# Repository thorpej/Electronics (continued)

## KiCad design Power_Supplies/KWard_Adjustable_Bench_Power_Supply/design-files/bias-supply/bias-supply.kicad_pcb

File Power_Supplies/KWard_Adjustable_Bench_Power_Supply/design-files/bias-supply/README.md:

# Bias supply

The bias supply board provides an adjustable (0 - -100V), current-limted
(approximately 30mA) negative bias supply for the device-under-test, typically
used to bias the power output stages of an amplifier.

The board is powered by a a Triad F4-120 power transfomer, which is nominally
rated as 115Vac -> 120Vac @ 50ma.

The AC input is rectified by a Rectron DB107 diode bridge chip, filtered, and
fed to a MJE5371 PNP power transistor which provides a low-impedance voltage
reference by pinning its base to -150V using a Zener diode.  This -150V reference
voltage is then fed to a second MJE5371, whose base voltage is controlled by a
fixed 39K resistor and a precision 10-turn potentiometer (see note below),
providing the variable bias voltage output.  A 1µF film cap at the output shunts
out any noise.

Current limiting is provided by a small KSA1013 PNP transistor (connected to the
base of the second MJE5371) and a 22 Ohm resistor.  As the current increases, the
voltage drop across the 22 Ohm resistor increases, which gradually turns on the
KSA1013, which pulls the base of the second MJE5371 closer to GND (more positive),
thus making the bias voltage output less negative.  Note that this is a gradual
effect; if there is significant load on the bias supply, it will become gradually
more difficult to pull the voltage further negative.

Beacuse the second MJE5371 can drop considerable voltage depending on the desired
bias output voltage selected, it can dissipate quite a bit more heat than the first
MJE5371 used as the voltage reference.  It is therefore mounted to a much beefier
heat sink than the first MJE5371.  Space for a small fin-type heat sink for the
first MJE5371 is provided, along with a specific Aavid part known to fit the
footprint.  Other small fin-type heat sinks may also fit in the alloted space.
However, it is important that the two heat sinks DO NOT TOUCH, unless the MJE5371s
are mounted using a TO-220 insulated mounting kit (plastic screw bushing + mica sheet).

The board includes protection diodes for the 3 transistors as well as the output.

Note: The voltage adjustment divider also contains a 10 Ohm fixed resistor to "back-stop"
the negative bias voltage because without it, the voltage can become positive with
the potentiometer at the full CCW position in simulation.  With this resistor in-place,
you may not be able to get the bias voltage to exactly 0V.  This may vary slightly
due to manufacturing tolerances.  If this is problematic for your application, feel
free to experiment with different resistor values, or to bypass the resistor entirely
with a jumper wire.

The board has standard M3 mounting holes, and is intended to be mounted on the
back of the PSU front panel using stand-offs.

## Parts list

Note that all resistors are 2W metal film unless specified otherwise.  The Mouser
part numbers provided here for standard resistors are for Vishay PR02-series, which
fit the footprints on the board.

* 1x Triad F4-120 power transformer or equivalent.
_Mouser part number 553-F4-120._
* 2x 2-position screw terminal blocks, 5.08mm pitch (CUI TB007-508-02BE or equivalent).
_Mouser part number 490-TB007-508-02BE._
* 2x 3-position screw terminal blocks, 5.08mm pitch (CUI TB006-508-03BE or equivalent).
_Mouser part number 490-TB006-508-03BE._
* 1x Rectron DB107 diode bridge (can substitude a Rectron DB105 or DB106, if desired).
_Mouser part number 583-DB107._
* 2x 220µF 250V electrolytic capacitor, up to 18mm diameter, 7.50mm lead spacing.
_Mouser part number 647-UCS2E221MHD._
* 1x 1µF 250V polypropylene film capacitor, rectangular form-factor, 18mm x 11mm, lead
spacing 15mm.
_Mouser part number 871-B32672L2105J000._
* 1x 1N5385B 150V 5W Zener diode.
_Mouser part number 863-1N5383BG._
* 4x 1N4007 diode.
_Mouser part number 621-1N4007G-T._
* 2x MJE5731 PNP transistors (TO-220 package).
_Mouser part number 863-MJE5731G._
* 1x KSA1013 PNP transistor (TO-92L package).
_Mouser part number 512-KSA1013YBU._
* 1x 100 Ohm resistor.
_Mouser part number 594-5083NW100R0JA100._
* 1x 330K Ohm resistor.
_Mouser part number 594-5083NW330K0J._
* 1x 10K Ohm resistor.
_Mouser part number 594-5083NW10K00J._
* 1x 39K Ohm resistor.
_Mouser part number 594-5083NW39K00J._
* 1x 10 Ohm resistor.
_Mouser part number 594-5083NW10R00J._
* 1x 22 Ohm resistor.
_Mouser part number 594-5083NW22R00J._
* 1x 1M Ohm resistor.
_Mouser part number 594-5083NW1M000F._
* 1x 100K 2W 10-turn panel-mount precision potentiometer.
_Mouser part number 652-3590S-2-104L._
* 1x Aavid Thermalloy ML33G TO-220 heat sink.
_Mouser part number 532-ML33G._
* 1x Aavid 577202B04000G TO-220 heat sink, or suitable substitute that
fits the available board space.
_Mouser part number 532-577202B04000G._
* **Optional but recommended** 2x insulated TO-220 mounting kit, such as
the Aavid 4880SG.
_Mouser part number 532-4880SG._

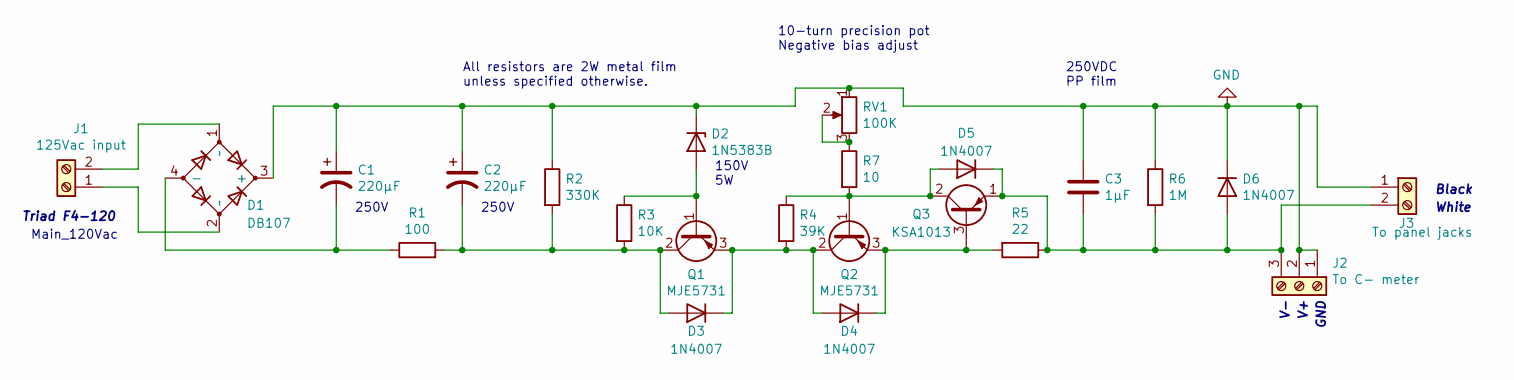
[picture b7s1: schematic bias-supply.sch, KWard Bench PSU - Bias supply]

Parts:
C1, C2: 220µF; CP_Radial_D18.0mm_P7.50mm; Mouser 647-UCS2E221MHD
C3: 1µF; C_Rect_L18.0mm_W11.0mm_P15.00mm_FKS3_FKP3; Mouser 871-B32672L2105J000
D1: DB107; Diode_Bridge_DIP-4_W7.62mm_P5.08mm
D2: 1N5383B; D_DO-201_P15.24mm_Horizontal; Mouser 863-1N5383BG
D3, D4, D5: 1N4007; D_DO-41_SOD81_P10.16mm_Horizontal
D6: 1N4007; D_DO-41_SOD81_P10.16mm_Horizontal; Mouser 621-1N4007G-T
J1: 125Vac input; TerminalBlock_bornier-2_P5.08mm
J2: To C- meter; TerminalBlock_bornier-3_P5.08mm
J3: To panel jacks; TerminalBlock_bornier-2_P5.08mm
Q1, Q2: MJE5731; TO-220-3_Vertical; Mouser 863-MJE5731G
Q3: KSA1013; TO-92L; Mouser 512-KSA1013YBU
R1: 100; R_Axial_DIN0411_L9.9mm_D3.6mm_P15.24mm_Horizontal; Mouser 594-5083NW100R0JA100
R2: 330K; R_Axial_DIN0411_L9.9mm_D3.6mm_P15.24mm_Horizontal; Mouser 594-5083NW330K0J
R3: 10K; R_Axial_DIN0411_L9.9mm_D3.6mm_P15.24mm_Horizontal; Mouser 594-5083NW10K00J
R4: 39K; R_Axial_DIN0411_L9.9mm_D3.6mm_P15.24mm_Horizontal; Mouser 594-5083NW39K00J
R5: 22; R_Axial_DIN0411_L9.9mm_D3.6mm_P15.24mm_Horizontal; Mouser 594-5083NW22R00J
R6: 1M; R_Axial_DIN0411_L9.9mm_D3.6mm_P15.24mm_Horizontal; Mouser 594-5083NW1M000F
R7: 10; R_Axial_DIN0309_L9.0mm_D3.2mm_P2.54mm_Vertical; Mouser 594-5083NW10R00J
RV1: 100K; TerminalBlock_bornier-3_P5.08mm

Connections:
GND: C1.1, C2.1, C3.1, D1.3 (+), D2.1 (K), D6.1 (K), J2.1, J2.2, J3.1, R2.1, R6.1, RV1.1
unnamed: C1.2, D1.4 (-), R1.1
unnamed: C2.2, D3.2 (A), Q1.2 (C), R1.2, R2.2, R3.2
unnamed: C3.2, D5.1 (K), D6.2 (A), J2.3, J3.2, Q3.1 (E), R5.1, R6.2
unnamed: D1.1 (~~), J1.2
unnamed: D1.2 (~~), J1.1
unnamed: D2.2 (A), Q1.1 (B), R3.1
unnamed: D3.1 (K), D4.2 (A), Q1.3 (E), Q2.2 (C), R4.2
unnamed: D4.1 (K), Q2.3 (E), Q3.3 (B), R5.2
unnamed: D5.2 (A), Q2.1 (B), Q3.2 (C), R4.1, R7.2
unnamed: R7.1, RV1.2, RV1.3

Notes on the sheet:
250V
150V 5W
10-turn precision pot Negative bias adjust
250VDC PP film
White
Black
All resistors are 2W metal film unless specified otherwise.
Triad F4-120
Main_120Vac
GND

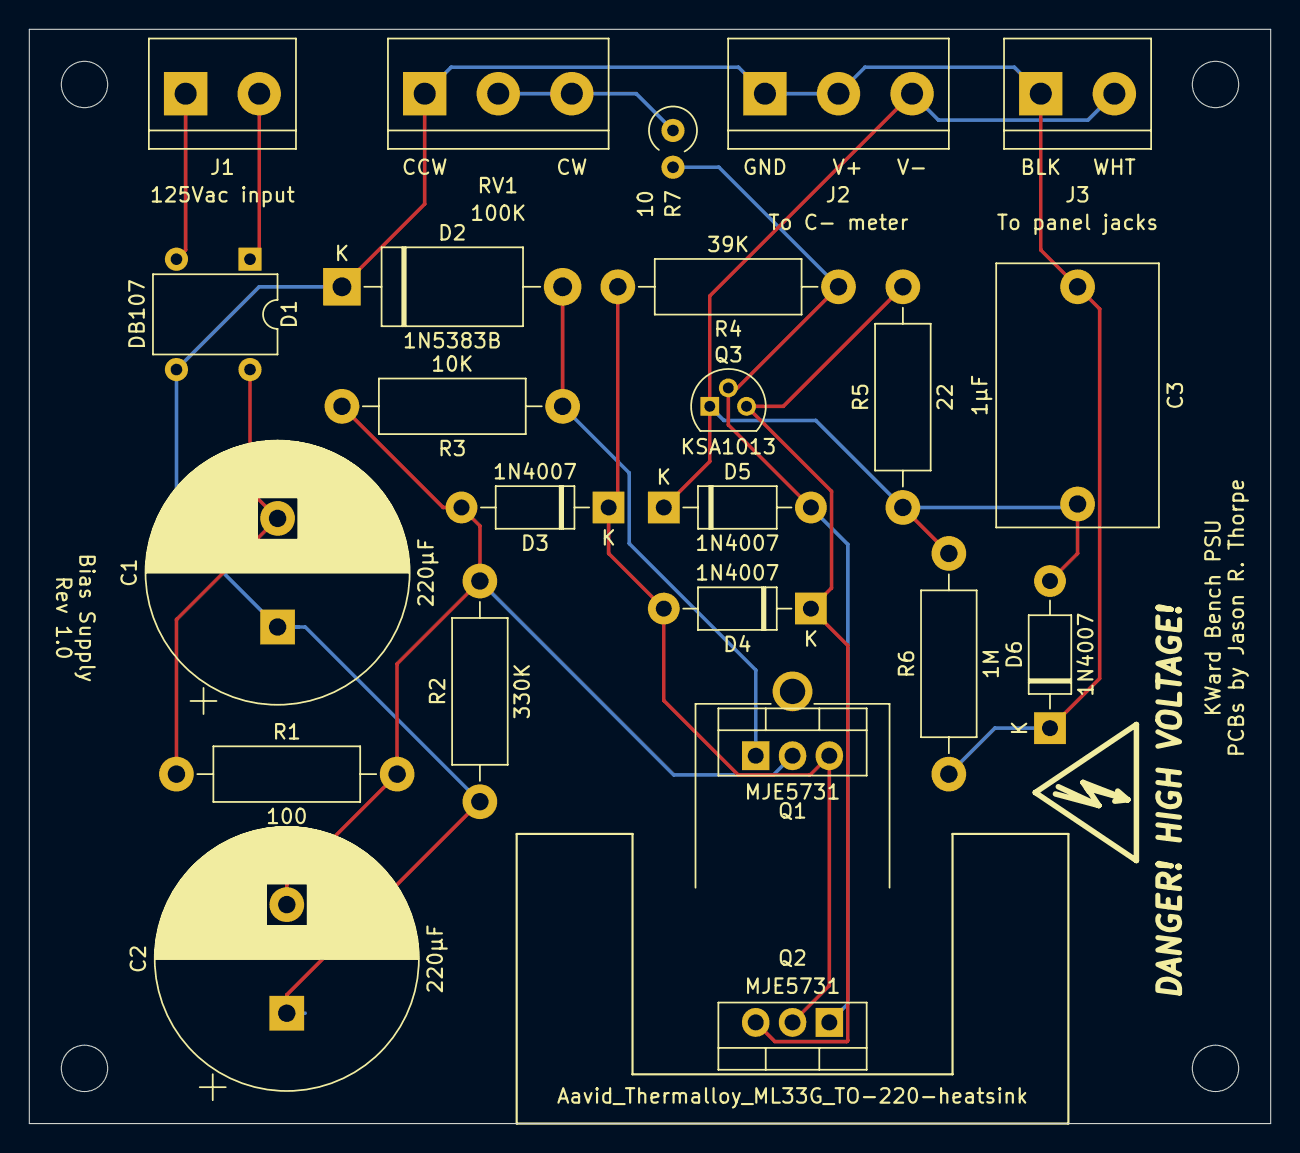
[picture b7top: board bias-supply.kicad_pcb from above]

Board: 2 copper layers, 85.7 x 75.6 mm, 24 parts (0 on the bottom side), 11 nets.

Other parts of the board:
**REF: Aavid_Thermalloy_ML33G_TO-220-heatsink

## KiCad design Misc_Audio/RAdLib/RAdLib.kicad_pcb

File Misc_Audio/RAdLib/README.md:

# The RAdLib - An OPL2 FM synthesizer board for Raspberry Pi

**NOTE: This is a work-in-progress.  Watch this space for updates.**

This project is an attempt to bring the glorious sound of the classic
AdLib sound card to the Raspberry Pi (and other single-board computers
with a compatible 40-pin GPIO header).  If you think this is a dumb
idea, you're right!  The purpose of the project is really to teach myself
and practice some design techniques and apply them to a piece of obsolete
technology with no practical application other than one of simple amusement.

My intent is for the board to be, to the extent possible, "100% software-
compatible" with the original AdLib, which was esentially the thinnest of
wrappers around the YM3812 "OPL2" synthesizer chip.  Practically speaking,
this means exposing all of the same capabilities of the OPL2 synthesizer
to the host system; obviously there are going to be some software-visible
differences because the Raspberry Pi does not have an ISA bus.

The OPL2 synthesizer circuit is essentially lifted from Sergey Malinov's
[ISA OPL2 Card](http://www.malinov.com/Home/sergeys-projects/isa-opl2-card),
and the analog section of the board is inspired by it, but has been reworked
to fit within the constraints of the Raspberry Pi's power supply.  The
bus interface, of course, is completely different.

## Bus Interface

The original AdLib is an 8-bit ISA card with fairly straight-forward address
decode logic that allows it to be accessed at one of 4 jumper-selectable
I/O-mapped addresses.  It occupies 2 bytes of I/O space.  The address decode
logic on the board is responsible for asserting the OPL2's /CS signal, and
the OPL2's /RD, /WR, and A0 signals are responsible for selecting which
internal register the bus cycle will access.  The OPL2 also has 8 data
signals, D[0-7].  /CS, /RD, and /WR are active-low.  The OPL2 responds
to these signals as follows:

* /CS=0, /RD=1, /WR=0, A0=0: write to the OPL2 index register (selects
which internal register to access)
* /CS=0, /RD=1, /WR=0, A0=1: write to the OPL2 data register (writes
this data to the previously selected internal register)
* /CS=0, /RD=0, /WR=1, A0=0: read the OPL2 status register
* /CS=1, /RD=x, /WR=x, A0=x: D[0-7] are high-Z
* The result of all other signal combinations is undefined.

As you can see, sending a command to the OPL2 requires two write cycles
(one for the index register, one for the data register).

The original AdLib is also capable of interrupting the host in the event
the host wants to use the built-in timers.  This was achieved by routing
the open-drain /IRQ signal of the OPL2 though a 7404 inverter to drive
one of the jumper-selected active-high ISA IRQ lines.

On the original AdLib, the clock is derived from the ISA bus clock.  We
have no such clock on the Raspberry Pi, so the clock is provided by a
3.58MHz crystal oscillator module in a DIP-8 "half-can" package.

Even though practically all software for the OPL2 treats it as a write-only
device, there is a status register that is accessed when you issue a read
cycle with the A0 pin low.  The only documented function of this status
register is to report if the OPL2 is asserting its interrupt line,
and which of the 2 timers is responsible for the interrupt.  I wasn't able
to find any (modern) software that actually uses the timer (and interrupt)
capabilities of the OPL2.  The only use for reading the status register I've
seen is for using undocumented bits to determine if the chip is an OPL2 or
OPL3.  But one of my goals was for the board to be able to do everything the
original AdLib could do, and that included reading the status register and
generating an interrupt.

At the bare minimum, there are 8 data lines and 5 non-data lines (A0,
READ/WRITE, CS, RESET, and IRQ) needed to interface to the OPL2.
Technically, the OPL2 has separate inputs for READ and WRITE, but a single
signal from the host can be used to generate both.  The data lines need to
be bi-directional.  A0, READ/WRITE, CS, and RESET are host->OPL2, and IRQ
is OPL2->host.  All of the control signals except A0 are active-low on the
OPL2.

I initially considered using SPI as the data interface between the host
and the RAdLib.  But this would have required an additional logic to trigger
loading of parallel-to-serial shift register from the OPL D[0..7] pins at
the right time after the OPL /CS and /RD signals are asserted in the read
case (which as stated before, is exceedingly rare).  The software overhead
of setting up the SPI transfers for each OPL2 register access also seemed
like it could be excessive and possibly difficult to avoid unpredictable
(software) timing artifacts.  It would have been hardware-intensive, as well;
2 shift registers (one for each direction) would have been required.

So, I scrapped the SPI idea and decided to go with a naive
drive-each-Dx-pin-directly approach.

Before we get into the details, here are the signals between the Raspberry
Pi and the OPL2 used by the RAdLib:

* D[0-7]: Bi-directional data signals
* A0: Address bit 0 (active high)
* READ: Indicates that the bus cycle is a READ access (active high)
* /CS: Chip-select (active low)
* /RST: OPL2 reset (active low)

The main challenge interfacing the OPL2 to the Raspberry Pi is that the
OPL2 is a CMOS device that uses 5V TTL logic levels, whereas the Raspberry
Pi's GPIO uses 3.3V CMOS logic levels.  This is not a problem for writing
to the OPL2, because a 3.3V CMOS logical "1" is 2.4V, which is above the
2V input threshold of TTL.  However, it is a problem if you want to be
able to read the OPL2 status register.  To support reading the OPL2 data
lines (which may output voltages in excess of 3.3V) safely, we need some
logic to level-shift the 5V TTL data signals from the OPL2 down to 3.3V CMOS
logic levels.  For this we use a 74LVC245A bus transceiver.  The 74LVC245A's
Vcc is connected to the 3.3V rail and has 5.5V-tolerant inputs.  The
transciever passes through the 3.3V signals on writes to the OPL2 and
level-shifts the signals from the OPL2 on reads.  The OPL2 is connected
to the "A" side of the 74LVC245A, and the Raspberry Pi is connected to
the "B" side.

The A0, /CS, and /RST control signals can be connected directly to the OPL2.

The READ signal needs to be converted into two discrete active-low control
signals for the OPL2: /RD and /WR.  Conveniently, READ being low translates
directly to /WR, and so it is directly connected to the OPL2.  We also
connect this signal to the DIR pin of the 74LVC245A.  When READ is low, B
is the input and A is the output.  When the READ signal goes high, A is
the input and B is the output.  That just leaves generating the /RD signal
at the OPL2.  This is achieved by connecting the OPL2 /RD pin to Vcc with
a 4.7K resistor and to GND using a discrete MOSFET.  The MOSFET is turned
on by the READ signal going high, which pulls the OPL2 /RD pin to GND.

## Active Filter

The original AdLib features an active low-pass filter comprised of 2
op-amps in a Butterworth configuration.  Simulation of this circuit
shows a voltage gain of 8dB with a flat response to 10KHz, is 3dB down
at 15KHz, and is 10dB down at 20KHz.

Unfortunately, the performance of this circuit relies on the headroom
afforded by the +12V/-12V split rail supply available on the ISA bus.
No such headroom is available on the Raspberry Pi; all we have is a
+5V rail.

The YM3014B DAC outputs a signal from 1/4 Vcc to 3/4 Vcc.  This means a
maximum output sine wave is centered at +2.5V and has a voltage swing of
2.5Vpp (slightly higher than a standard consumer line-level output).  This
leaves us with very little headroom to amplify the signal for the filter.

This required a re-work of the 2-stage active low-pass filter.  The reworked
filter achieves unity gain and performance similar to that of the original
filter circuit, but requires the use of a rail-to-rail op-amp; the OP495
is the most expensive part on the board.

## Audio Output Section

The original AdLib also includes an LM386 audio power amplifier IC connected
to the +12V/-12V rails to drive headphones or a small loudspeaker.  Again, the
Raspberry Pi does not have adequate power supply headroom in order to provide
any voltage gain, so we will have to be content with the 2.5Vpp swing we get
from the DAC, and rely on an external power amplifier with a line-level
input to drive a loudspeaker.  However, I still wanted to include a volume
control.  The high side of the volume control pot is AC-coupled to the output
of the filter circuit, and the wiper is AC-coupled to an emitter-follower
to isolate the volume control from the load connected to the output jack.
AC coupling is used on either side of the volume control to deep DC off of
the pot (no one likes scratchy volume controls).  The 2N3904 is biased with
a voltage divider taken off the +5V rail.  This should be capable of driving
any line-level output, and may also be able to drive headphones to some degree.

As built, unfortunately, this uses 3 large electrolytic caps to maintain
the flat frequency response, but I don't think it's the end of the world.

## Bill of Materials

You can source most of the components at Mouser.  Here are links to
individual components that fit the footprints on the board.

All resistors are 1/8W 1%.

* 6x .1uF ceramic capacitor (C1, C2, C3, C4, C201, C203) [Mouser 81-RHSN12A104K1DGH1A](https://www.mouser.com/ProductDetail/81-RHSN12A104K1DGH1A)
* 4x 10uF tantalum capacitor (C5, C6, C7, C51, C202) [Mouser 581-TAP106K016SCS](https://www.mouser.com/ProductDetail/581-TAP106K016SCS)
* 1x 680pF ceramic capacitor (C52) [Mouser 81-RCER72A681K0DBH3A](https://www.mouser.com/ProductDetail/81-RCER72A681K0DBH3A)
* 2x 1000pF ceramic capacitor (C53, C56) [Mouser 81-RCER72A102K0DBH3A](https://www.mouser.com/ProductDetail/81-RCER72A102K0DBH3A)
* 2x 100pF ceramic capacitor (C54, C57) [Mouser 594-K101K15C0GH5TK2](https://www.mouser.com/ProductDetail/594-K101K15C0GH5TK2)
* 1x 470pF ceramic capacitor (C55) [Mouser 81-RCER72A471K0DBH3A](https://www.mouser.com/ProductDetail/81-RCER72A471K0DBH3A)
* 3x 220uF electrolytic capacitor (C58, C59, C61) [Mouser 75-516D227M016MM6AE3](https://www.mouser.com/ProductDetail/75-516D227M016MM6AE3)
* 1x .047uF ceramic capacitor (C60) [Mouser 81-RCER72A473K1DBH3A](https://www.mouser.com/ProductDetail/81-RCER72A473K1DBH3A)
* 1x 10-position break-away 2.54mm vertical header (J2, J3, J4, JP1) [Mouser 538-22-28-5101](https://www.mouser.com/ProductDetail/538-22-28-5101)
* 1x Audio jack (J5) [Mouser 806-STX-31203B577C](https://www.mouser.com/ProductDetail/806-STX-31203B577C)
* 1x 2N3904 NPN transistor (Q1) [Mouser 610-2N3904](https://www.mouser.com/ProductDetail/610-2N3904)
* 1x 2N7000 N-channel MOSFET (Q201) [Mouser 512-2N700](https://www.mouser.com/ProductDetail/512-2N7000)
* 5x 10K resistor (R1, R2, R3, R4, R9) [Mouser 270-10K-RC](https://www.mouser.com/ProductDetail/270-10K-RC)
* 2x 1K resistor (R5, R7) [Mouser 270-1K-RC](https://www.mouser.com/ProductDetail/270-1K-RC)
* 1x 2.7K resistor (R6) [Mouser 270-2.7K-RC](https://www.mouser.com/ProductDetail/270-2.7K-RC)
* 3x 10R resistor (R8, R10, R11) [Mouser 270-10-RC](https://www.mouser.com/ProductDetail/270-10-RC)
* 5x 3.3K resistor (R201, R202, R203, R204, R205) [Mouser 270-3.3K-RC](https://www.mouser.com/ProductDetail/270-3.3K-RC)
* 1x 10K audio taper potentiometer (RV1) [Mouser 652-91A1A-B24-D15L](https://www.mouser.com/ProductDetail/652-91A1A-B24-D15L)
* 1x OP495 op-amp (U3) [Mouser 584-OP495GPZ](https://www.mouser.com/ProductDetail/584-OP495GPZ)
* 1x 74LVC245A bus transciever (U201) [Mouser 595-SN74LVC245ANE4](https://www.mouser.com/ProductDetail/595-SN74LVC245ANE4)
* 1x XXX 24Cxx serial EEPROM (U204) (optional)
* 1x DIP-8 3.579545MHz crystal oscillator (X1) [Mouser 520-TCH357X](https://www.mouser.com/ProductDetail/520-TCH357-X)

I sourced the female connector that mates to the Raspberry Pi from
Adafruit.  If someone has a Mouser part # for an equivalent part,
please share it with me!

* 1x Tall 2x20 female header (J1) [Adafruit 1992](https://www.adafruit.com/product/1992)

Things you'll need to find yourself (on eBay, perhaps):

* 1x Yamaha YM3812 (U1)
* 1x Yamaha YM3014B (U2)

I provisioned space for sockets for the expensive / old-stock / optional ICs.
You can get these from Jameco, Amazon, etc.

* YM3812 (U1) - DIP-24 15.24mm
* YM3014B (U2) - DIP-8 7.62mm
* OP495 (U3) - DIP-14 7.62mm
* 24Cxx (U204) (optional) - DIP-8 7.62mm

**NOTE: This is a work-in-progress.  Watch this space for updates.**

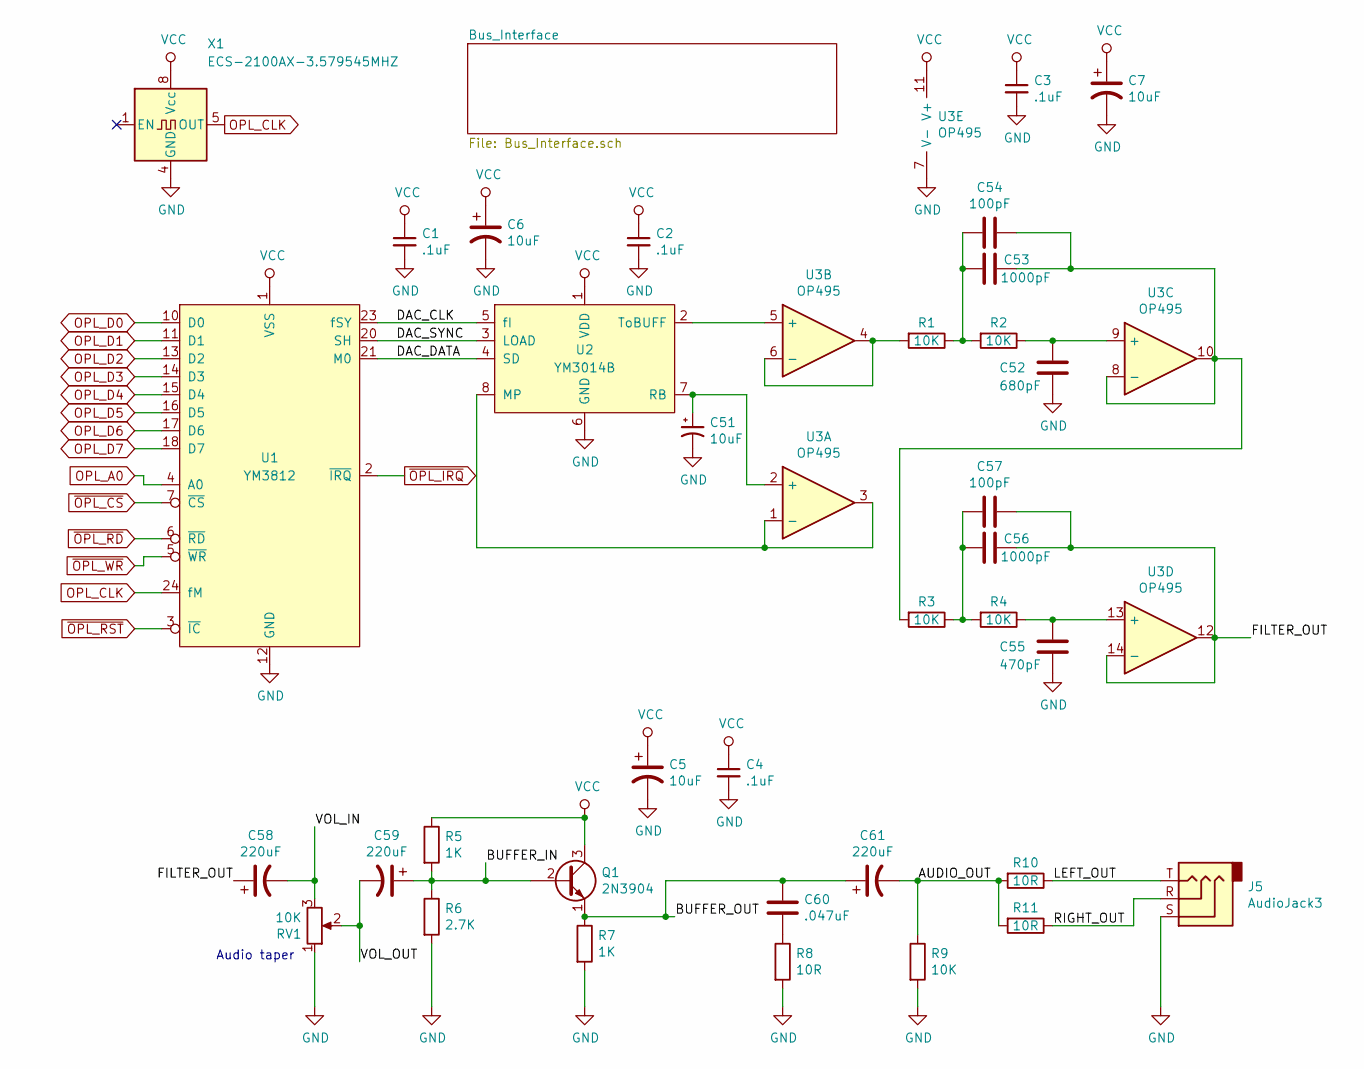
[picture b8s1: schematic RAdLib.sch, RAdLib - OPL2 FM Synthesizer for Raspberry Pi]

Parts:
C1, C2, C3, C4: .1uF; C_Disc_D5.0mm_W2.5mm_P2.50mm
C5, C6, C7: 10uF; CP_Radial_D5.0mm_P2.50mm
C51: 10uF; CP_Radial_D5.0mm_P2.50mm; Part AVX TAP106K016SCS
C52: 680pF; C_Disc_D5.0mm_W2.5mm_P2.50mm
C53, C56: 1000pF; C_Disc_D5.0mm_W2.5mm_P2.50mm
C54, C57: 100pF; C_Disc_D5.0mm_W2.5mm_P2.50mm
C55: 470pF; C_Disc_D5.0mm_W2.5mm_P2.50mm
C58, C59, C61: 220uF; CP_Axial_L18.0mm_D8.0mm_P25.00mm_Horizontal
C60: .047uF; C_Disc_D5.0mm_W2.5mm_P2.50mm
J5: AudioJack3; Jack_3.5mm_STX-3120-3B; Part Kycon STX-3120-3B-577C
Q1: 2N3904; TO-92_HandSolder
R1, R2, R3, R4, R9: 10K; R_Axial_DIN0204_L3.6mm_D1.6mm_P5.08mm_Horizontal
R5, R7: 1K; R_Axial_DIN0204_L3.6mm_D1.6mm_P5.08mm_Horizontal
R6: 2.7K; R_Axial_DIN0204_L3.6mm_D1.6mm_P5.08mm_Horizontal
R8, R10, R11: 10R; R_Axial_DIN0204_L3.6mm_D1.6mm_P5.08mm_Horizontal
RV1: 10K; Potentiometer_Bourns_91A1x_A24; Part Bourns 91A1A-B24-D15L
U1: YM3812; DIP-24_W15.24mm_Socket
U2: YM3014B; DIP-8_W7.62mm_Socket
U3: OP495; DIP-14_W7.62mm_Socket
X1: ECS-2100AX-3.579545MHZ; Oscillator_DIP-8; Part ECS-2100AX-3.579545MHZ

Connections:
+5V: C1.1, C2.1, C3.1, C4.1, C5.1, C6.1, C7.1, Q1.3 (C), R5.1, U1.1 (VSS), U2.1 (VDD), U3.11 (V+), X1.8 (Vcc); also elsewhere on the board
/AUDIO_OUT: C61.2, R9.1, R10.2, R11.2
/BUFFER_IN: C59.1, Q1.2 (B), R5.2, R6.1
/BUFFER_OUT: C60.1, C61.1, Q1.1 (E), R7.1
/DAC_CLK: U1.23 (fSY), U2.5 (fI)
/DAC_DATA: U1.21 (M0), U2.4 (SD)
/DAC_SYNC: U1.20 (SH), U2.3 (LOAD)
/FILTER_OUT: C56.1, C57.1, C58.1, U3.12, U3.14 (-)
/LEFT_OUT: J5.T, R10.1
/RIGHT_OUT: J5.R, R11.1
/VOL_IN: C58.2, RV1.3; also elsewhere on the board
/VOL_OUT: C59.2, RV1.2; also elsewhere on the board
GND: C1.2, C2.2, C3.2, C4.2, C5.2, C6.2, C7.2, C51.2, C52.2, C55.2, J5.S, R6.2, R7.2, R8.2, R9.2, RV1.1, U1.12 (GND), U2.6 (GND), U3.7 (V-), X1.4 (GND); also elsewhere on the board
unnamed: C51.1, U2.7 (RB), U3.2 (+)
unnamed: C52.1, R2.1, U3.9 (+)
unnamed: C53.1, C54.1, R3.2, U3.8 (-), U3.10
unnamed: C53.2, C54.2, R1.1, R2.2
unnamed: C55.1, R4.1, U3.13 (+)
unnamed: C56.2, C57.2, R3.1, R4.2
unnamed: C60.2, R8.1
unnamed: R1.2, U3.4, U3.6 (-)
unnamed: U2.2 (ToBUFF), U3.5 (+)
unnamed: U2.8 (MP), U3.1 (-), U3.3
OPL_A0: U1.4 (A0); also elsewhere on the board
OPL_CLK: U1.24 (fM), X1.5 (OUT)
OPL_D0: U1.10 (D0); also elsewhere on the board
OPL_D1: U1.11 (D1); also elsewhere on the board
OPL_D2: U1.13 (D2); also elsewhere on the board
OPL_D3: U1.14 (D3); also elsewhere on the board
OPL_D4: U1.15 (D4); also elsewhere on the board
OPL_D5: U1.16 (D5); also elsewhere on the board
OPL_D6: U1.17 (D6); also elsewhere on the board
OPL_D7: U1.18 (D7); also elsewhere on the board
~OPL_CS: U1.7 (~CS); also elsewhere on the board
~OPL_IRQ: U1.2 (~IRQ); also elsewhere on the board
~OPL_RD: U1.6 (~RD); also elsewhere on the board
~OPL_RST: U1.3 (~IC); also elsewhere on the board
~OPL_WR: U1.5 (~WR); also elsewhere on the board

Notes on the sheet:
Audio taper

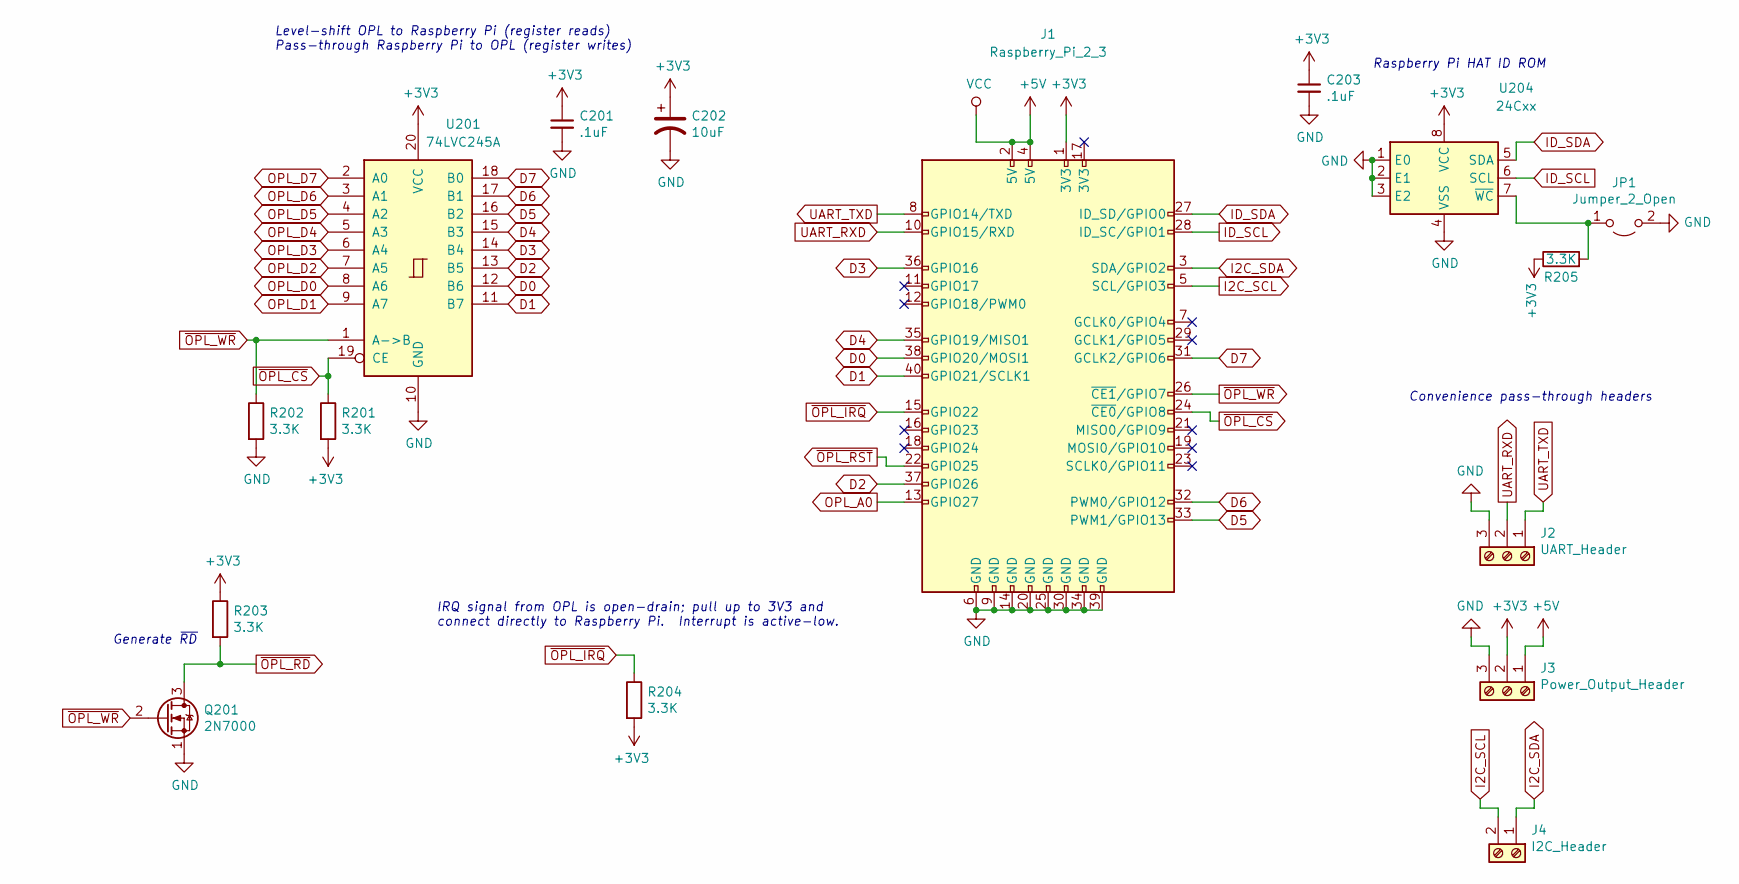
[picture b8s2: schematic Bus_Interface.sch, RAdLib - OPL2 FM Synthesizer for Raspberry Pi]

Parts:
C201, C203: .1uF; C_Disc_D5.0mm_W2.5mm_P2.50mm
C202: 10uF; CP_Radial_D5.0mm_P2.50mm
J1: Raspberry_Pi_2_3; PinHeader_2x20_P2.54mm_Vertical
J2: UART_Header; PinHeader_1x03_P2.54mm_Vertical
J3: Power_Output_Header; PinHeader_1x03_P2.54mm_Vertical
J4: I2C_Header; PinHeader_1x02_P2.54mm_Vertical
JP1: Jumper_2_Open; PinHeader_1x02_P2.54mm_Vertical
Q201: 2N7000; TO-92_HandSolder
R201, R202, R204: 3.3K; R_Axial_DIN0204_L3.6mm_D1.6mm_P5.08mm_Horizontal; Part Xicon 270-3.3K/REEL-RC
R203, R205: 3.3K; R_Axial_DIN0204_L3.6mm_D1.6mm_P5.08mm_Horizontal
U201: 74LVC245A; DIP-20_W7.62mm
U204: 24Cxx; DIP-8_W7.62mm_Socket

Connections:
+3V3: C201.1, C202.1, C203.1, J1.1 (3V3), J3.2, R201.2, R203.1, R204.2, R205.1, U201.20 (VCC), U204.8 (VCC)
+5V: J1.2 (5V), J1.4 (5V), J3.1; also elsewhere on the board
D0: J1.38 (GPIO20/MOSI1), U201.12 (B6)
D1: J1.40 (GPIO21/SCLK1), U201.11 (B7)
D2: J1.37 (GPIO26), U201.13 (B5)
D3: J1.36 (GPIO16), U201.14 (B4)
D4: J1.35 (GPIO19/MISO1), U201.15 (B3)
D5: J1.33 (PWM1/GPIO13), U201.16 (B2)
D6: J1.32 (PWM0/GPIO12), U201.17 (B1)
D7: J1.31 (GCLK2/GPIO6), U201.18 (B0)
GND: C201.2, C202.2, C203.2, J1.6 (GND), J1.9 (GND), J1.14 (GND), J1.20 (GND), J1.25 (GND), J1.30 (GND), J1.34 (GND), J1.39 (GND), J2.3, J3.3, JP1.2 (B), Q201.1 (S), R202.2, U201.10 (GND), U204.1 (E0), U204.2 (E1), U204.3 (E2), U204.4 (VSS); also elsewhere on the board
I2C_SCL: J1.5 (SCL/GPIO3), J4.2
I2C_SDA: J1.3 (SDA/GPIO2), J4.1
ID_SCL: J1.28 (ID_SC/GPIO1), U204.6 (SCL)
ID_SDA: J1.27 (ID_SD/GPIO0), U204.5 (SDA)
unnamed: JP1.1 (A), R205.2, U204.7 (~WC)
OPL_A0: J1.13 (GPIO27); also elsewhere on the board
OPL_D0: U201.8 (A6); also elsewhere on the board
OPL_D1: U201.9 (A7); also elsewhere on the board
OPL_D2: U201.7 (A5); also elsewhere on the board
OPL_D3: U201.6 (A4); also elsewhere on the board
OPL_D4: U201.5 (A3); also elsewhere on the board
OPL_D5: U201.4 (A2); also elsewhere on the board
OPL_D6: U201.3 (A1); also elsewhere on the board
OPL_D7: U201.2 (A0); also elsewhere on the board
UART_RXD: J1.10 (GPIO15/RXD), J2.2
UART_TXD: J1.8 (GPIO14/TXD), J2.1
~OPL_CS: J1.24 (~CE0~/GPIO8), R201.1, U201.19 (CE); also elsewhere on the board
~OPL_IRQ: J1.15 (GPIO22), R204.1; also elsewhere on the board
~OPL_RD: Q201.3 (D), R203.2; also elsewhere on the board
~OPL_RST: J1.22 (GPIO25); also elsewhere on the board
~OPL_WR: J1.26 (~CE1~/GPIO7), Q201.2 (G), R202.1, U201.1 (A->B); also elsewhere on the board

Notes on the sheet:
Level-shift OPL to Raspberry Pi (register reads) Pass-through Raspberry Pi to OPL (register writes)
Generate ~RD
Raspberry Pi HAT ID ROM
Convenience pass-through headers
IRQ signal from OPL is open-drain; pull up to 3V3 and connect directly to Raspberry Pi. Interrupt is active-low.

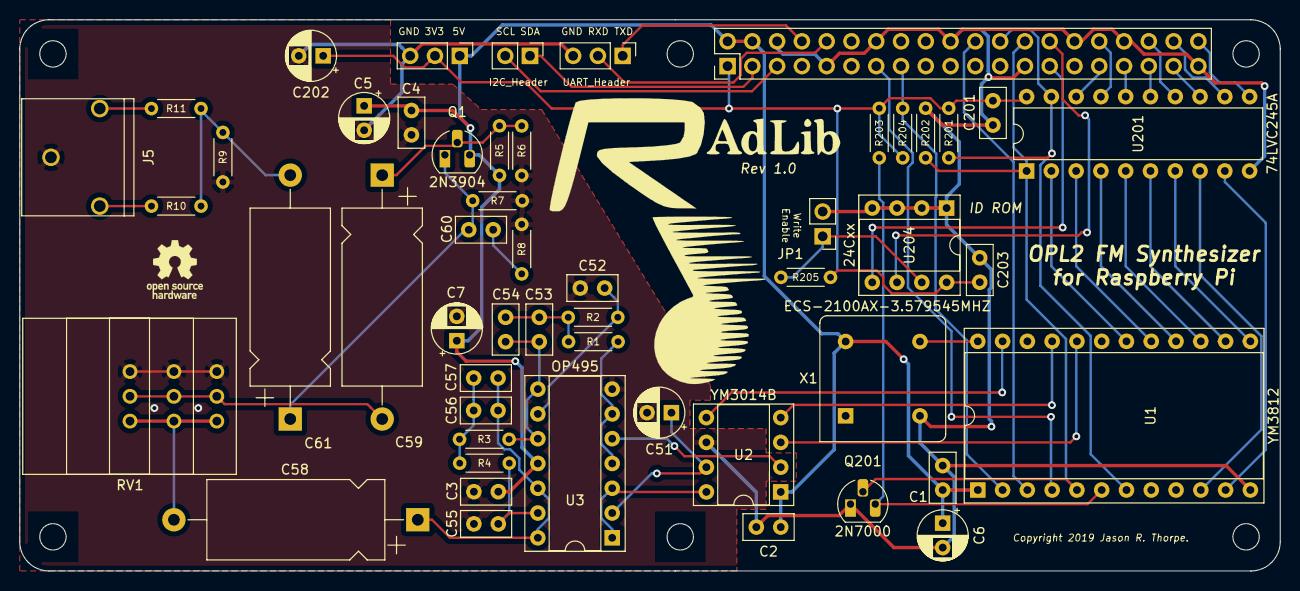
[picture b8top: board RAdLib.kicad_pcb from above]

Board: 2 copper layers, 129.2 x 56.5 mm, 54 parts (0 on the bottom side), 54 nets.

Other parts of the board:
RV1#2, RV1#3: 10K; Potentiometer_Bourns_91A1x_A24

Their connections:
/VOL_IN: RV1#2.3, RV1#3.3; also elsewhere on the board
/VOL_OUT: RV1#2.2, RV1#3.2; also elsewhere on the board
GND: RV1#2.1, RV1#3.1; also elsewhere on the board

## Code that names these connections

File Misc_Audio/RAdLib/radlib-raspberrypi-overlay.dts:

/*-
 * Copyright (c) 2019 Jason R. Thorpe.
 * All rights reserved.
 *
 * Redistribution and use in source and binary forms, with or without
 * modification, are permitted provided that the following conditions
 * are met:
 * 1. Redistributions of source code must retain the above copyright
 *    notice, this list of conditions and the following disclaimer.
 * 2. Redistributions in binary form must reproduce the above copyright
 *    notice, this list of conditions and the following disclaimer in the
 *    documentation and/or other materials provided with the distribution.
 *
 * THIS SOFTWARE IS PROVIDED BY THE AUTHOR ``AS IS'' AND ANY EXPRESS OR
 * IMPLIED WARRANTIES, INCLUDING, BUT NOT LIMITED TO, THE IMPLIED WARRANTIES
 * OF MERCHANTABILITY AND FITNESS FOR A PARTICULAR PURPOSE ARE DISCLAIMED.
 * IN NO EVENT SHALL THE AUTHOR BE LIABLE FOR ANY DIRECT, INDIRECT,
 * INCIDENTAL, SPECIAL, EXEMPLARY, OR CONSEQUENTIAL DAMAGES (INCLUDING,
 * BUT NOT LIMITED TO, PROCUREMENT OF SUBSTITUTE GOODS OR SERVICES;
 * LOSS OF USE, DATA, OR PROFITS; OR BUSINESS INTERRUPTION) HOWEVER CAUSED
 * AND ON ANY THEORY OF LIABILITY, WHETHER IN CONTRACT, STRICT LIABILITY,
 * OR TORT (INCLUDING NEGLIGENCE OR OTHERWISE) ARISING IN ANY WAY
 * OUT OF THE USE OF THIS SOFTWARE, EVEN IF ADVISED OF THE POSSIBILITY OF
 * SUCH DAMAGE.
 */

#include <dt-bindings/pinctrl/bcm2835.h>
#include <dt-bindings/gpio/gpio.h>
#include <dt-bindings/interrupt-controller/irq.h>

/*
 * Device tree overlay for the RAdLib -- an OPL2 FM synthesizer for
 * Raspberry Pi.
 *
 * This overlay is for Raspberry Pi systems with a 40-pin GPIO header.
 */

/*
 * The RAdLib uses the following GPIO pins [header pin #]:
 *
 * Bi-directional signals:
 * OPL D0	GPIO20 [38]
 * OPL D1	GPIO21 [40]
 * OPL D2	GPIO26 [37]
 * OPL D3	GPIO16 [36]
 * OPL D4	GPIO19 [35]
 * OPL D5	GPIO13 [33]
 * OPL D6	GPIO12 [32]
 * OPL D7	GPIO6  [31]
 *
 * Output-only signals:
 * OPL A0	GPIO27 [13]
 * READ		GPIO7  [26]
 * OPL /CS	GPIO8  [24]
 * OPL /RST	GPIO25 [22]
 *
 * Input-only signals:
 * /IRQ		GPIO22 [15]
 */

#define	OPL_D0		20
#define	OPL_D1		21
#define	OPL_D2		26
#define	OPL_D3		16
#define	OPL_D4		19
#define	OPL_D5		13
#define	OPL_D6		12
#define	OPL_D7		6

#define	OPL_A0		27
#define	OPL_READ	7
#define	OPL_CS		8
#define	OPL_RST		25

#define	OPL_IRQ		22

/dts-v1/;
/plugin/;
/ {
	compatible = "brcm,bcm2837", "brcm,bcm2836", "brcm,bcm2835";

	fragment@0 {
		target = <&gpio>;
		__overlay__ {
			radlib_Dx_output: radlib-Dx-output-pins {
				brcm,pins = <OPL_D0 OPL_D1 OPL_D2 OPL_D3,
				    OPL_D4 OPL_D5 OPL_D6 OPL_D7>;
				brcm,function = <BCM2835_FSEL_GPIO_OUT>;
				brcm,pull = <BCM2835_PUD_OFF>;
			};
			radlib_Dx_input: radlib-Dx-input-pins {
				brcm,pins = <OPL_D0 OPL_D1 OPL_D2 OPL_D3,
				    OPL_D4 OPL_D5 OPL_D6 OPL_D7>;
				brcm,function = <BCM2835_FSEL_GPIO_IN>;
				brcm,pull = <BCM2835_PUD_OFF>;
			};

			radlib_ctrl_output: radlib-ctrl-output-pins {
				brcm,pins = <OPL_A0 OPL_READ OPL_CS OPL_RST>;
				brcm,function = <BCM2835_FSEL_GPIO_OUT>;
				brcm,pull = <BCM2835_PUD_OFF>;
			};
			radlib_ctrl_disabled: radlib-ctrl-disabled {
				/*
				 * Configure /CS as an input and pull
				 * it high so that the OPL2 will be
				 * inert until the driver attaches.
				 */
				brcm,pins = <OPL_CS OPL_RST>;
				brcm,function = <BCM2835_FSEL_GPIO_IN>;
				brcm,pull = <BCM2835_PUD_UP>;
			};

			radlib_irq_input: radlib-irq-input-pins {
				brcm,pins = <OPL_IRQ>;
				brcm,function = <BCM2835_FSEL_GPIO_IN>;
				brcm,pull = <BCM2835_PUD_OFF>;
			};
		};
	};

	fragment@1 {
		target-path = "/";
		__overlay__ {
			radlib-opl2 {
				compatible = "thorpej,radlib-opl2";

				interrupt-parent = <&gpio>;
				interrupts = <OPL_IRQ IRQ_TYPE_LEVEL_LOW>;

				pinctrl-names = "default",
				    "data-outputs", "data-inputs",
				    "control-outputs", "irq-inputs";
				pinctrl-0 = <&radlib_ctrl_disabled>;
				pinctrl-1 = <&radlib_Dx_output>;
				pinctrl-2 = <&radlib_Dx_input>;
				pinctrl-3 = <&radlib_ctrl_output>;
				pinctrl-4 = <&radlib_irq_input>;

				data-gpios = <&gpio OPL_D0 GPIO_ACTIVE_HIGH>,
					     <&gpio OPL_D1 GPIO_ACTIVE_HIGH>,
					     <&gpio OPL_D2 GPIO_ACTIVE_HIGH>,
					     <&gpio OPL_D3 GPIO_ACTIVE_HIGH>,
					     <&gpio OPL_D4 GPIO_ACTIVE_HIGH>,
					     <&gpio OPL_D5 GPIO_ACTIVE_HIGH>,
					     <&gpio OPL_D6 GPIO_ACTIVE_HIGH>,
					     <&gpio OPL_D7 GPIO_ACTIVE_HIGH>;

				a0-gpios = <&gpio OPL_A0 GPIO_ACTIVE_HIGH>;

				read-gpios = <&gpio OPL_READ GPIO_ACTIVE_HIGH>;

				cs-gpios = <&gpio OPL_CS GPIO_ACTIVE_LOW>;

				rst-gpios = <&gpio OPL_RST GPIO_ACTIVE_LOW>;
			};
		};
	};
};

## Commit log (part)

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2018-03-18 Create LICENSE
2018-03-18 Add high-voltage warning.
2018-03-20 Initial commit of the adjustable bench power supply files.
2018-03-21 Fix typo.
2018-03-23 Add my IN-14 breadout board.
2018-03-30 Expand on how to select the correct current-limiting resistor.
2018-03-31 Add a link to a photo of the board in action.
2018-04-12 Initial version of a user-space driver for the Taos TSL2561 Lux sensor.
    This is initially targeted at NetBSD, and uses the NetBSD i2c
    API to access the device. But it should be pretty easily adapted
    to other platforms.
2018-04-12 Fix typo in Makefile that prevented incorrect dependency generation.
2018-04-12 Disable auto-gain when the gain is set manually.
2018-04-12 Add the README file.
2018-04-12 Yet another typo.
2018-04-12 Fix return type of tsl256x_free().
2018-05-27 In tsl256x_poweron(), verify that the power-on cycle completed by reading back the control register.
2018-05-27 Oops, fix a paste-o, and make tsl256x_read1() available. (I back-ported this change from another version of this driver.)
2018-05-27 In tsl256x_set_integration_time(), if writing to the register fails, ensure that we power the device back off.
2018-05-27 Note the existence of the tsllux(4) kernel-mode driver on NetBSD.
2018-08-26 Fix a tyop.
2018-09-16 Add Rev 1.1 of my bias-balance helper board.
2018-09-21 Add a link to the spreadsheet's location on Github to make it easier to download for the casual reader.
2018-09-21 Make Raw_Bias_Voltage swing +/- 15%, rather than 12.5%.
2018-09-21 Tidy up the ASCII cart a little.
2018-09-21 It's not the Qpoint voltage that's brought out to Vneg, it's the Raw_Neg_Voltage. Update the documentation and calculator to reflect this reality.
2018-09-21 Add a simulation for a bias adjustment network that uses a single pot for each individual output tube in a stereo push-pull application.
2018-09-21 Some edits from Kevin, plus some extra verbiage about what changes would be needed for high bias voltage applications.
2018-09-22 Add a bias-balance network simulation.
2018-09-22 Add links to / descriptions of the two bias/balance network simulations.
2018-09-22 Change to the actual values I plan to use in my 1625 / 807 amp.
2018-09-23 Add KiCad files and resulting Gerber files for the EFB bias supply board.
2018-09-24 Remove a spurious "is".
2018-09-26 Add a LICENSE file specific to EFB(tm) boards.
2018-09-26 Minor grammar tweak.
2018-10-03 Oops, remove from junk text from an earlier revision that snuck through.
2018-10-03 Remove more bogus text left over from a previous revision.
2018-10-30 tsl256x_free() takes a tsl256x_t, not a tsl256x_t *.
2018-11-25 Initial add of my user-space PCA9685 LED controller driver.
2018-11-26 Fix description of when pca9685_set_freq() and pca9685_set_output_mode() can / must be called.
2019-07-19 WIP of an API for displaying stuff on Nixie displays. More to come.
2019-07-20 Fix dumb obo error.
2019-07-20 Add a new function to set a byte value at the specified index.
2019-07-20 Add a "counting" mode for testing / debugging.
2019-07-20 Bump copyright year.
2019-07-21 Provide more details about what sorts of BCD decoder chips this code will work with.
2019-07-21 Shorten the delay.
2019-09-17 Add symbols for various IC, Nixies, power nodes, regulators, and valves I have lurking around.
2019-09-17 Fix the cathode names for the IV-22.
2019-09-20 Add a symbol for my 2ChanCCSLoad board.
2019-09-20 Add a library for switches. First entry is for C&K A20403RNZQ 2-pole 4-position rotary switch.
2019-09-20 Footprint for leaded radial electrolytic, 25mm diameter, 12.5mm pin pitch. E.g. Nichicon UPT2D821MRD
2019-09-21 Add my 6AS7 pre-amp design. WIP -- not yet ready for fabrication.
2019-09-24 Checkpoint -- getting closer to laying out the tone control PCB.
2019-09-24 A couple of small tweaks for laying out the PCB.
2019-09-24 Adjust ground plane top and bottom.
2019-09-24 Removed the heater circuit sheet -- that has been spun off into a separate project.
2019-09-24 Add a Danger - High Voltage symbol for F.SilkS
2019-09-24 Add high voltage warnings.
2019-09-24 Final tweaks and Gerbers for the PCBs.
2019-09-25 Rev the CCS tail board -- use the Bourns 4-turn trim pots, and shrink the board a bit.
2019-09-25 Add my 2-channel CCS plate load board, a companion to the 2-channel CCS tail board.
2019-09-25 Add a symbol for my CCS_Tail_x2 board.
2019-09-25 Add a LICENSE file.
2019-09-25 Add LICENSE files.
2019-09-29 Add LTSpice simulation files for the pre-amp circuit and the PSU.
2019-09-30 Oops, the input buffer / tone controls are on a +250V rail in the final schematic, not a +300V rail. Adjust the simulation to correct this.
2019-10-01 Initial commit of the EEPROM-28 firmware.
2019-10-01 Bump version, fix a comment.
2019-10-08 Add 74HC165, tweak background on a couple of other symbols.
2019-10-08 Add a PCB template for a Rasperry Pi HAT. See:
    https://github.com/raspberrypi/hats/blob/master/hat-board-mechanical.pdf
2019-10-09 Make the RPI connector J1.
2019-10-12 Add a couple of useful graphics.
2019-10-13 Checkpoint ... board is close to being done. Still need to tweak the ground plane.
2019-10-14 Initial Raspberry Pi DT overlay for RAdLib.
2019-10-15 Add a draft overlay for the Libre All-H3-CC.
2019-10-18 Register ladder DAC simulation.
2019-10-19 Add an initial README file.
2019-10-22 Interrupt is now active-low.
2019-10-22 Fix the pin numbers on the pads of the Bourns pot.
2019-10-22 Add 74LVC245A.
2019-10-22 Reference LICENSE.txt.
2019-10-22 Update README to reflect the current revision of the board≥
2019-10-22 Add some capacitor footprints for the 6AS7 pre-amp board.
2019-10-22 C&K V80212MS02Q footprint.
2019-10-22 Remove /RST from the default "disabled" pinctrl configuration. It would need to be pulled *low*, not high like /CS.
2019-10-23 Describe how the bus interface works (or, rather, will work after I rework it).
2019-10-24 Additional tweaks, silly graphics.
2019-10-29 Add simulation of the analog section to be used on the RAdLib.
2019-10-30 Rework the audio output section as an AC-coupled emitter-follower.
2019-10-30 Add a note about why the volume control is AC-coupled on either side.
2019-10-30 Clarify what is borrowed.
2019-10-30 Update title block.
2019-11-23 Checkpoint.
2019-11-23 Fix some typos, etc.
2019-12-01 Oops, syntax errors in the gpio declarations.
2021-12-14 Add a Displays library, and plop in a Wurth WL-T7DS display module.
2021-12-16 Add a Displays footprint library, and put a simple footprint for the Wurth WL-T7DS single-digit unit in there.
2021-12-16 Add a symbol for the 74LS382A 4-bit simplified ALU.
2021-12-16 Symbol and footprint for the CUI PJ-097BH DC jack.
2021-12-16 Fix the pin names / visibility on the CUI DC jack.
2021-12-17 Make pad 1 square.
2021-12-17 Add a footprint for the NKK BB16AP switch.
2021-12-27 README.md: Add note about PCBs that will be done for this project.
2021-12-28 Add Rectron DB10x DIP-4 bridge rectifiers.
2021-12-28 DB10x: Make the + and - pins power outputs.
2021-12-28 Add first pass at schematic for bench PSU meter panel power supply.
2021-12-28 panel-supply: Small schematic tweaks made while laying out the PCB.
2021-12-29 Add a basic footprint for the Aavid Thermalloy ML33G TO-220 heat sink.
2021-12-29 KWard PSU: First pass at panel supply PCB.
2021-12-29 Correct footprint library name for the diode bridge.
2021-12-29 Add a 6550 symbol.
2021-12-29 Add a footprint to the 6550.
2021-12-29 Add the filament unit to the 6550.
2021-12-29 Add a 4-position 10.16mm-pitch screw terminal block footprint.
2021-12-30 First pass at the 6550 pass array board.
2021-12-31 Add a C_Rect_L18.0mm_W18.0mm_P15.0mm footprint.
2021-12-31 Use 100K sharing resistors in the cap stacks of the B+ supply.
2021-12-31 Schematic and PCB for the screen supply and regulator board.
2021-12-31 Schematic and PCB for the PSU bias supply.
2022-01-01 Reposition the measurements.
2022-01-01 AC input for the B+ supply is "B+_120Vac".
2022-01-01 Minor tweaks to the silk screen on the regulator board.
2022-01-01 Filament supply schematic.
2022-01-01 Add a README for the panel supply board.
2022-01-01 Improve text comments.
2022-01-02 Correct AC input value label, add some part numbers, tweak some text.
2022-01-02 Correct AC input value label, and change mounting holes to NPTH.
2022-01-02 Final tweaks for rev 1.0.
2022-01-02 README.md for the bias supply board.
2022-01-02 Add PDFs for bias supply schematic / pcb.
2022-01-02 Update copyright / license notice after discussion with Kevin.
2022-01-02 Missed one word substitution.
2022-01-02 Note that there are now some addtional design differences from Kevin's original. Move files into subdirectories to clean up the clutter.
2022-01-02 Call out the protection diodes.
2022-01-03 Some wording improvements based on feedback from Kevin.
2022-01-04 Add a footprint for the AES P-ST8-193 PC-mount octal tube socket.
2022-01-04 Split these into separate bottle sizes.
2022-01-04 Redo the pass tube array board, using the proper footprint for the AES ceramtic PC-mount octal socket.
2022-01-04 Generate Gerbers for pass tube array board
2022-01-05 Correct minor flaw in PCB.
2022-01-05 README for the pass tube array board.
2022-01-05 Add the tube socket part #.
2022-01-05 More working tweaks.
2022-01-05 Add my "snap-in capacitor stack" helper board.
2022-01-05 SnapInCapStack: Round the corders of the board.
2022-01-05 Part # tweaks (to reflect currently-available components).
2022-01-06 Spec United Chemi-Con E92L401VSN561MR65U caps for the first filter stage; the TDK parts previously listed are EoL.
2022-01-06 Add a README for the HV supply.
2022-01-06 Add a note about the power switch configuration for the B+ rail.
2022-01-06 Add PDF of the HV supply schematic.
2022-01-06 Add JPG image of PCB.
2022-01-06 Add a footprint for Rayex LB2 lugged relays.
2022-01-07 Add a symbol for Rayex LB2 DPDT relays.
2022-01-08 Initial device tree overlays.
2022-01-08 Fits on 8.5 x 11.
2022-01-08 Add PDFs / JPGs of the schematic and PCB, and add a README describing what this thing is.
2022-01-09 Increase trace clarance for the default net class to 0.3mm, and reroute several traces to meet new clearance requirements.
2022-01-10 Gegenerate PDF.
2022-01-16 Fix hilarious layout mistake -- swap the locations of C1 and C2. No functional difference, but it's what I originally intended, and is a little more intuitive.
2022-01-16 Move screw terminal labels further away from footprints to reduce the change they'll be obscrured by the terminal block.
2022-04-24 Add a Teensy 4.1 GPIO + power pins symbol.
2022-10-14 Add a symbol for the W65C21 PIA.
2022-10-15 Add 74LS164 shift register.
2022-10-16 Add a symbol for the AS6C6264.
2022-12-13 Added RPi Pico symbol / footprint (from RaspberryPi.org).
2022-12-14 Pure through-hole RPi Pico footprint.
2022-12-19 Add footprint for the Kobiconn_163-179PH 5.5 x 2.1 PCB-mount barrel jack.
2023-02-12 Add TR1863 UART.
2023-02-19 Add the NABU expansion header.
2023-02-19 STX-3128-B: Use pin numbers from the data sheet, and put T/R/S on the silk screen.
2023-02-20 Properlt decorate more of the NABU expansion header pins.
2023-04-30 Add AT28C16 and DS1813.
2023-05-31 Add a GAL22V10 symbol.
2023-06-25 Add symbols for the Ali Express FTDI break-out board that I like to use and the Adafruit FTDI Friend.
2023-06-25 Add DIP-18_W10.16mm_Socket.
2023-06-28 Add Adafruit Metro Mini.
2023-07-17 Add SNES game connector symbol and footprint.
2024-02-08 Add a symbol for the Commander X16 VERA module.
2024-02-08 Adjust location of symbol value.
2024-02-08 Add footprint to VERA module.
2024-02-08 Fix VERA mounting holes.
2024-02-08 Add VERA module PCB template.
2024-08-30 Add a bunch of symbols.
2025-06-26 Add memory symbols.
2025-06-26 Add a PGA169 socket footprint.
2025-06-26 Add ATF1508AS-TQFP
2025-06-26 Fix some missing pins on atf1508as-tqfp100
2025-06-29 Add CY7C1061GE-TSOP-II-54
2025-06-29 Rename the previous 68882 to 68882-PLCC. Add a new 68882 (bare name) in PGA68 package.
2025-06-29 Fix the /RESET pin on the 68882.
2025-07-09 Add RTL8019AS.
